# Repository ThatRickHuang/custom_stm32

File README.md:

# Custom STM32

Custom STM32 PCB design for KiCad 10.

Open `custom_stm32.kicad_pro` in KiCad to access the schematic and PCB layout.

- `custom_stm32.kicad_pro`: project settings.
- `custom_stm32.kicad_sch`: schematic recovered from local project history.
- `custom_stm32.kicad_pcb`: PCB layout.

Manufacturing exports, reference downloads, and local editor files are excluded from this repository.

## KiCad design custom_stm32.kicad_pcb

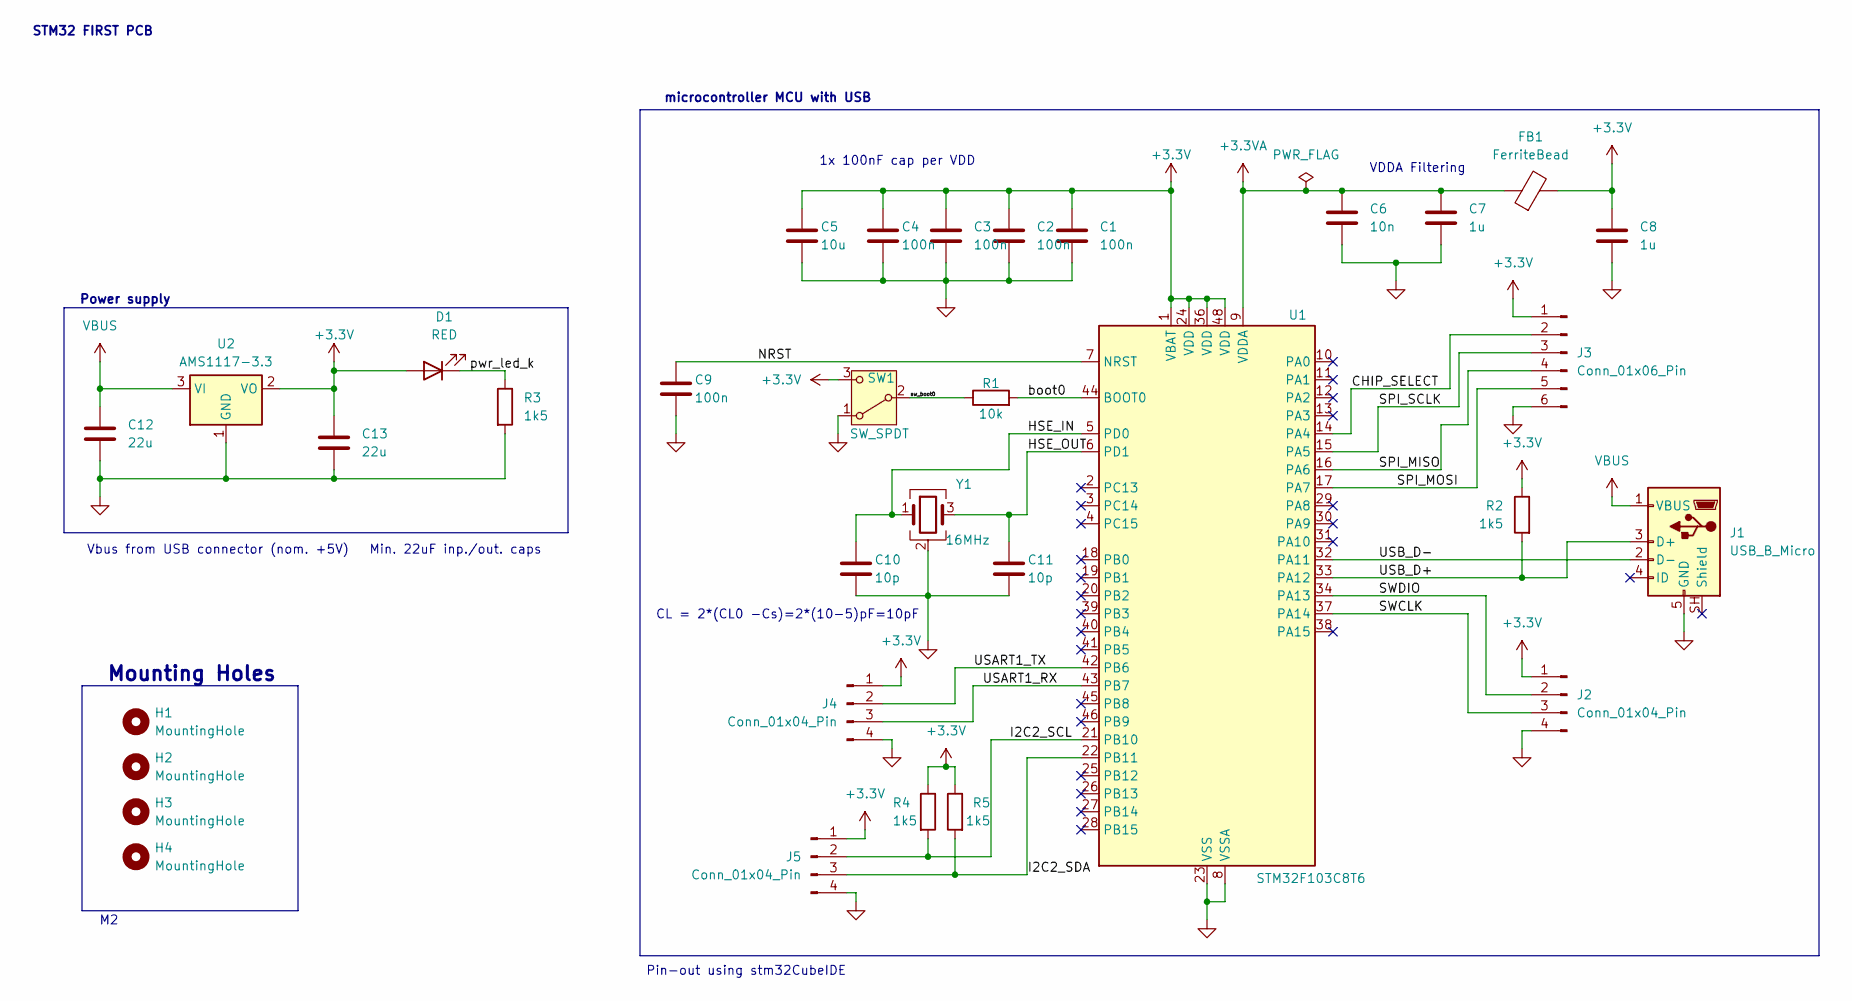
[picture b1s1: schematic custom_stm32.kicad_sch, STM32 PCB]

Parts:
C1, C2, C3, C4, C9: 100n; C_0402_1005Metric
C5: 10u; C_0603_1608Metric
C6: 10n; C_0402_1005Metric
C7, C8: 1u; C_0402_1005Metric
C10, C11: 10p; C_0402_1005Metric
C12, C13: 22u; C_0805_2012Metric
D1: RED; LED_0603_1608Metric
FB1: FerriteBead; L_0603_1608Metric
H1, H2, H3, H4: MountingHole; MountingHole_2.2mm_M2
J1: USB_B_Micro; USB_Micro-B_Wuerth_629105150521
J2, J4, J5: Conn_01x04_Pin; PinHeader_1x04_P2.54mm_Vertical
J3: Conn_01x06_Pin; PinHeader_2x03_P2.54mm_Vertical
R1: 10k; R_0402_1005Metric
R2, R3, R4, R5: 1k5; R_0402_1005Metric
SW1: SW_SPDT; SW_SPDT_PCM12
U1: STM32F103C8T6; LQFP-48_7x7mm_P0.5mm
U2: AMS1117-3.3; SOT-223-3_TabPin2
Y1: 16MHz; Crystal_SMD_Citizen_CS325S-4Pin_3.2x2.5mm

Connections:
+3.3V: C1.1, C2.1, C3.1, C4.1, C5.1, C8.1, C13.1, D1.2 (A), FB1.2, J2.1, J3.1, J4.1, J5.1, R2.1, R4.1, R5.1, SW1.3 (C), U1.1 (VBAT), U1.24 (VDD), U1.36 (VDD), U1.48 (VDD), U2.2 (VO)
+3.3VA: C6.1, C7.1, FB1.1, U1.9 (VDDA)
/CHIP_SELECT: J3.2, U1.14 (PA4)
/HSE_IN: C10.1, U1.5 (PD0), Y1.1
/HSE_OUT: C11.1, U1.6 (PD1), Y1.3
/I2C2_SCL: J5.2, R4.2, U1.21 (PB10)
/I2C2_SDA: J5.3, R5.2, U1.22 (PB11)
/NRST: C9.1, U1.7 (NRST)
/SPI_MISO: J3.4, U1.16 (PA6)
/SPI_MOSI: J3.5, U1.17 (PA7)
/SPI_SCLK: J3.3, U1.15 (PA5)
/SWCLK: J2.3, U1.37 (PA14)
/SWDIO: J2.2, U1.34 (PA13)
/USART1_RX: J4.3, U1.43 (PB7)
/USART1_TX: J4.2, U1.42 (PB6)
/USB_D+: J1.3 (D+), R2.2, U1.33 (PA12)
/USB_D-: J1.2 (D-), U1.32 (PA11)
/boot0: R1.2, U1.44 (BOOT0)
/pwr_led_k: D1.1 (K), R3.1
/sw_boot0: R1.1, SW1.2 (B)
GND: C1.2, C2.2, C3.2, C4.2, C5.2, C6.2, C7.2, C8.2, C9.2, C10.2, C11.2, C12.2, C13.2, J1.5 (GND), J2.4, J3.6, J4.4, J5.4, R3.2, SW1.1 (A), U1.8 (VSSA), U1.23 (VSS), U1.35 (VSS), U1.47 (VSS), U2.1 (GND), Y1.2 (G), Y1.4 (G)
VBUS: C12.1, J1.1 (VBUS), U2.3 (VI)

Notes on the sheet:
1x 100nF cap per VDD
STM32 FIRST PCB
CL = 2*(CL0 -Cs)=2*(10-5)pF=10pF
Vbus from USB connector (nom. +5V) Min. 22uF inp./out. caps
VDDA Filtering
microcontroller MCU with USB
Mounting Holes
Pin-out using stm32CubeIDE
Power supply

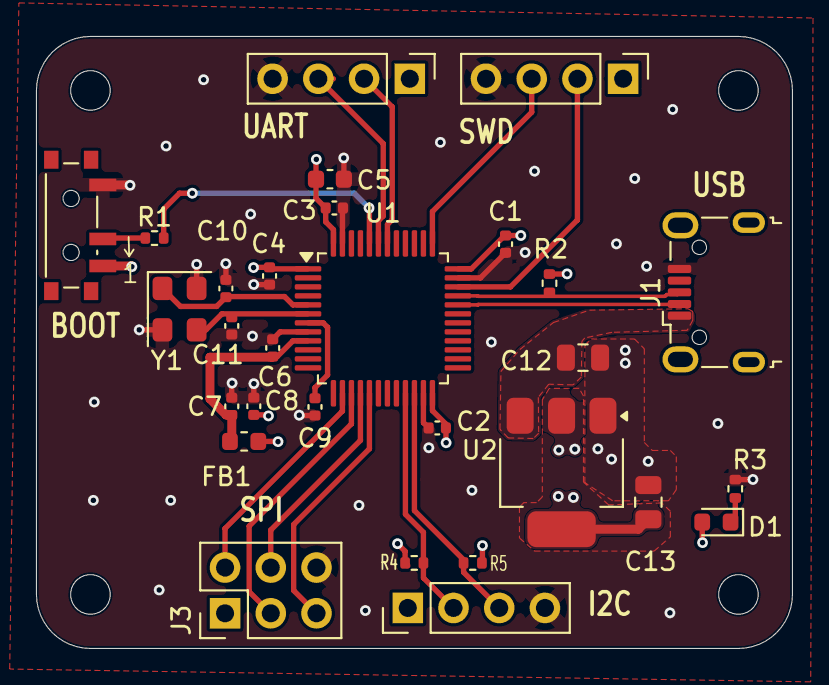
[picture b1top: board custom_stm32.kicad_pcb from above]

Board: 4 copper layers, 42.0 x 34.0 mm, 33 parts (0 on the bottom side), 22 nets.
